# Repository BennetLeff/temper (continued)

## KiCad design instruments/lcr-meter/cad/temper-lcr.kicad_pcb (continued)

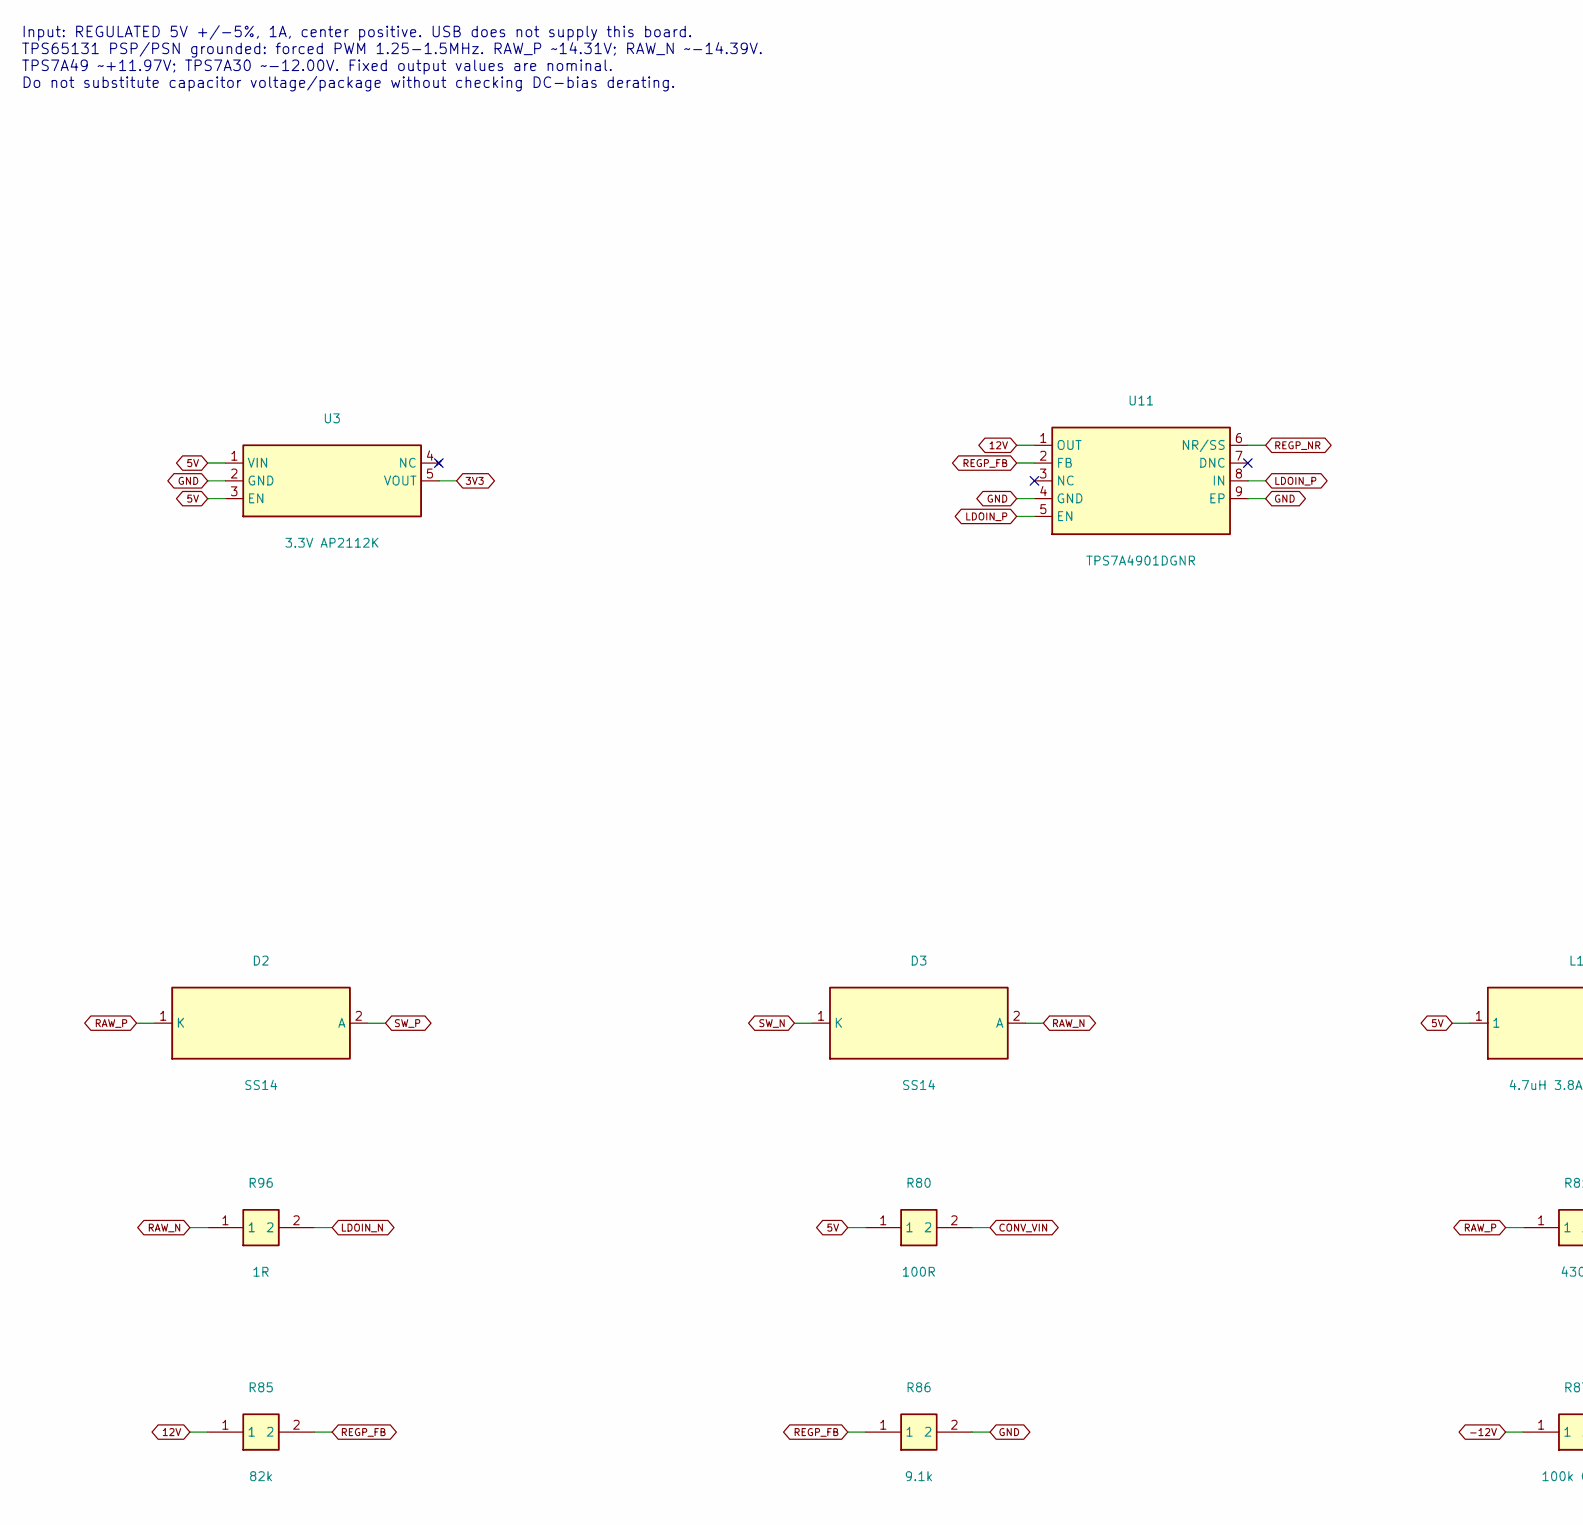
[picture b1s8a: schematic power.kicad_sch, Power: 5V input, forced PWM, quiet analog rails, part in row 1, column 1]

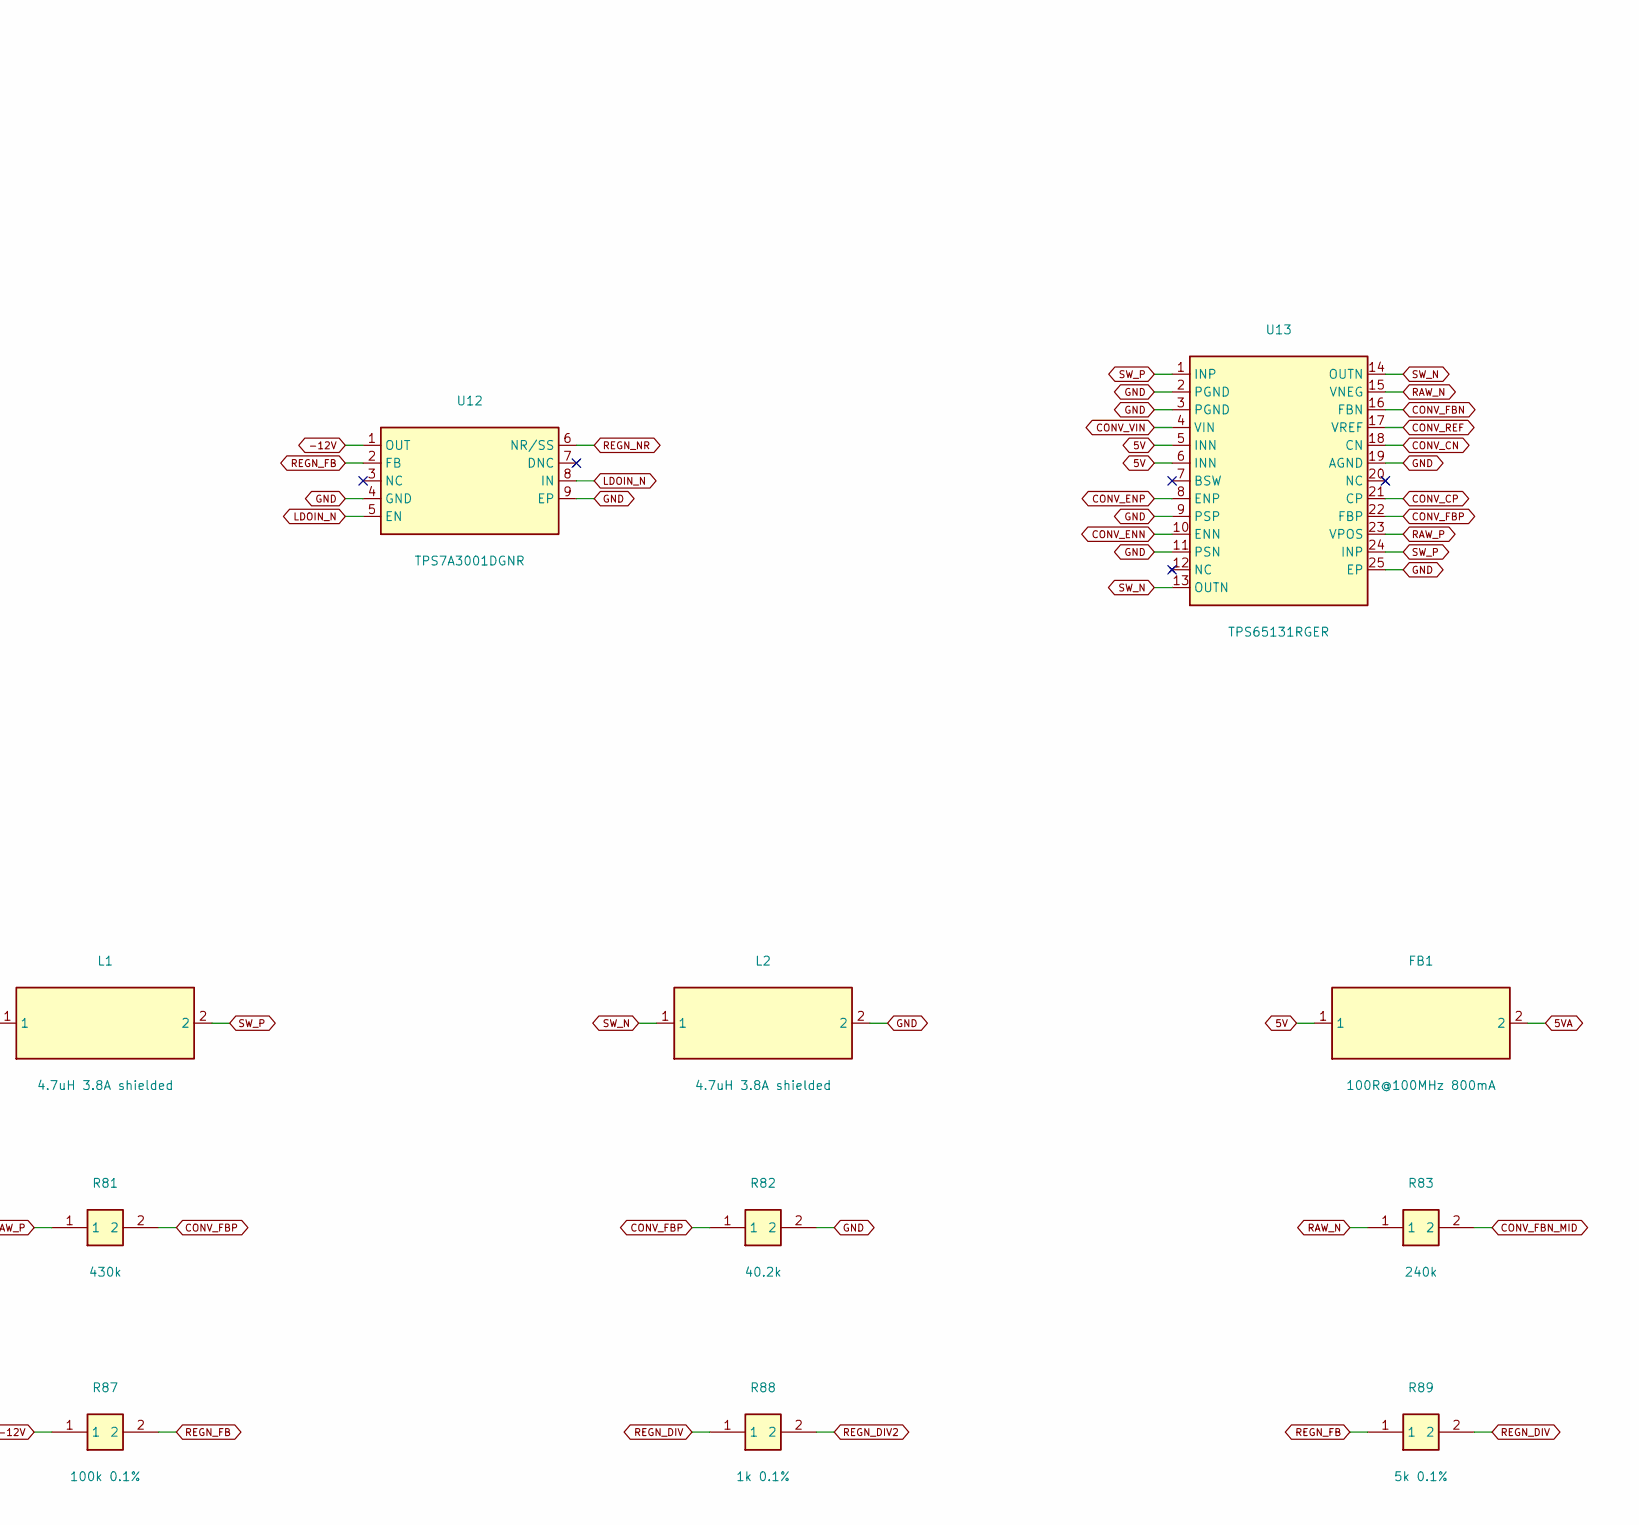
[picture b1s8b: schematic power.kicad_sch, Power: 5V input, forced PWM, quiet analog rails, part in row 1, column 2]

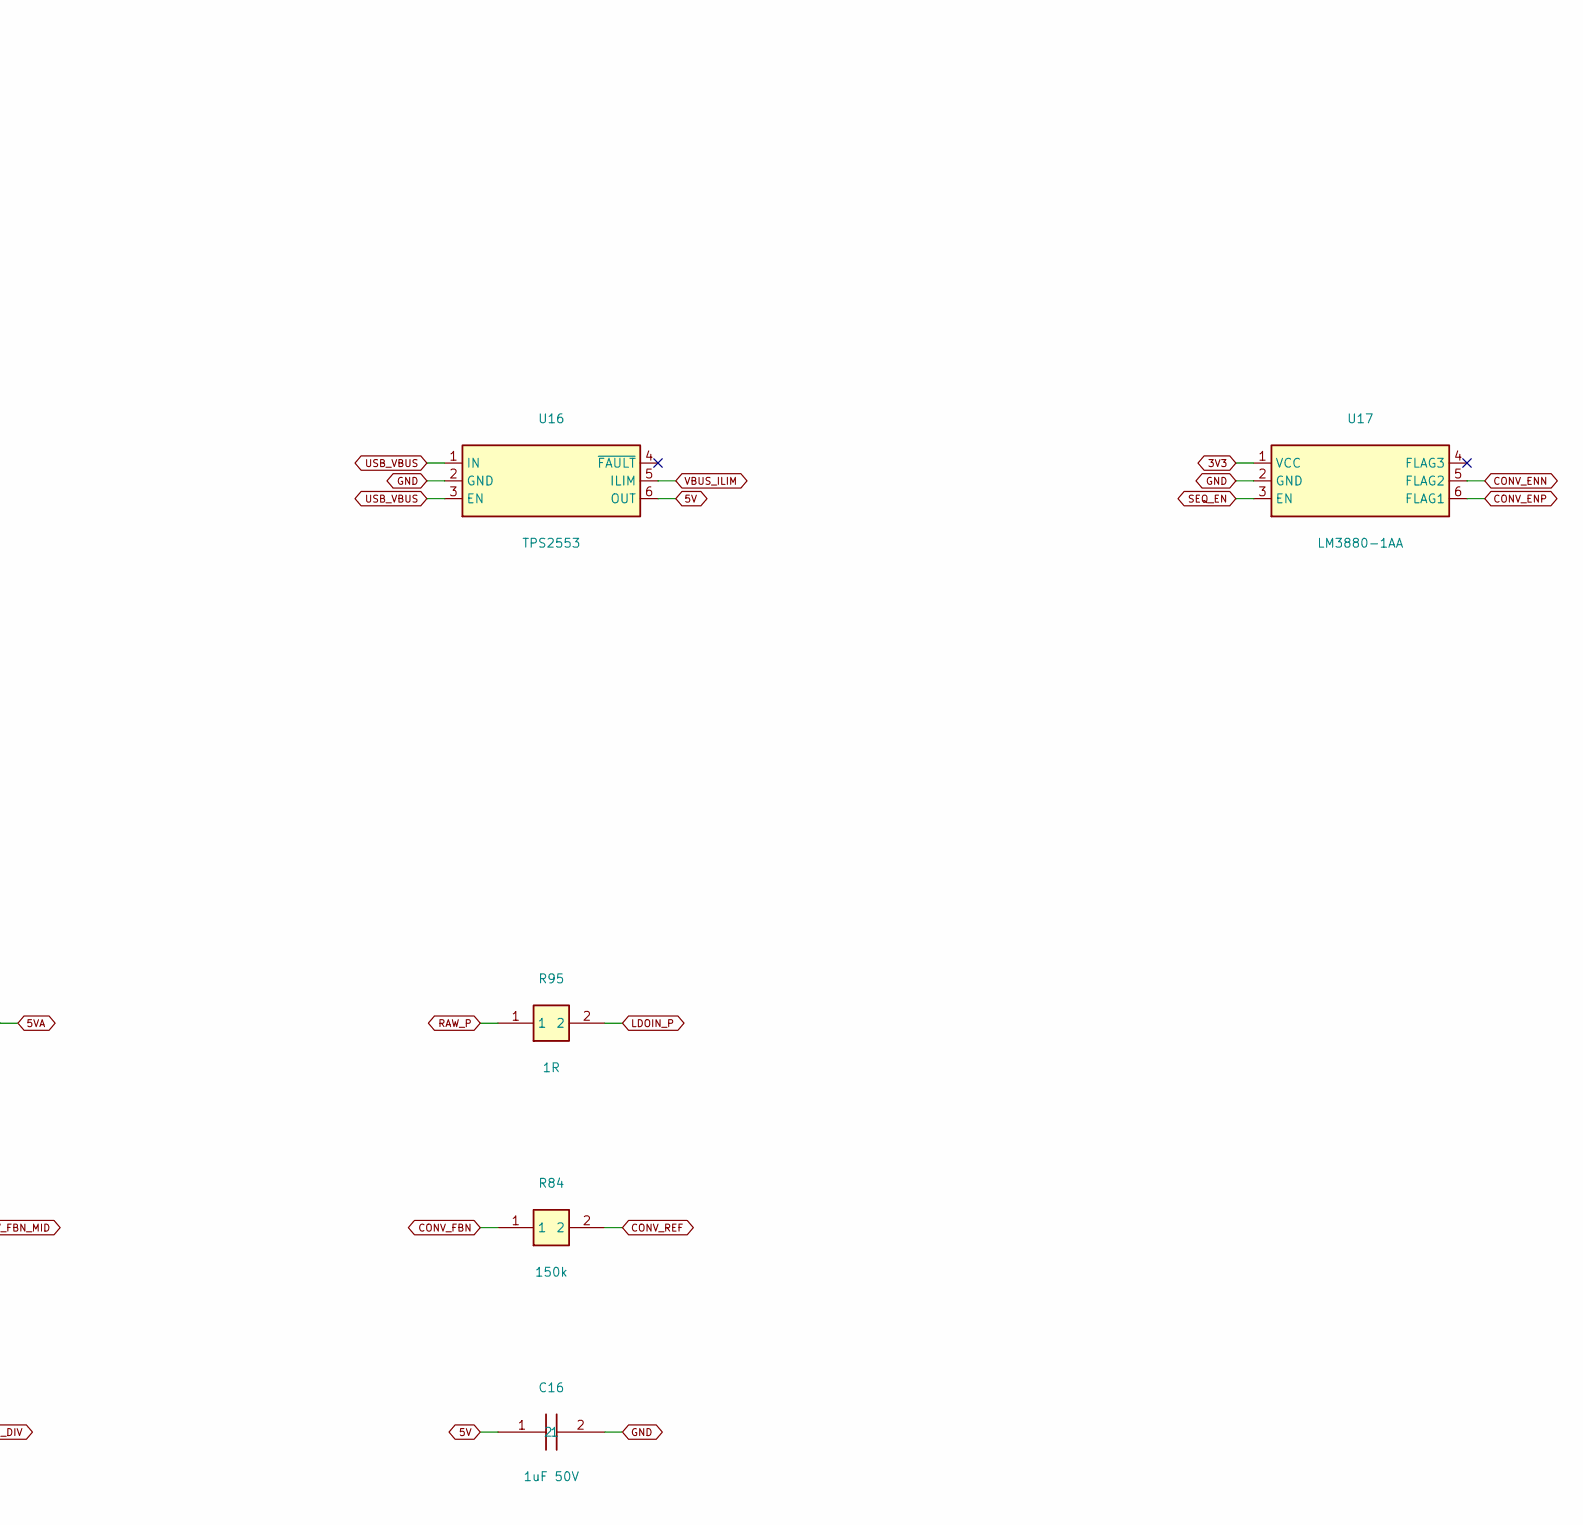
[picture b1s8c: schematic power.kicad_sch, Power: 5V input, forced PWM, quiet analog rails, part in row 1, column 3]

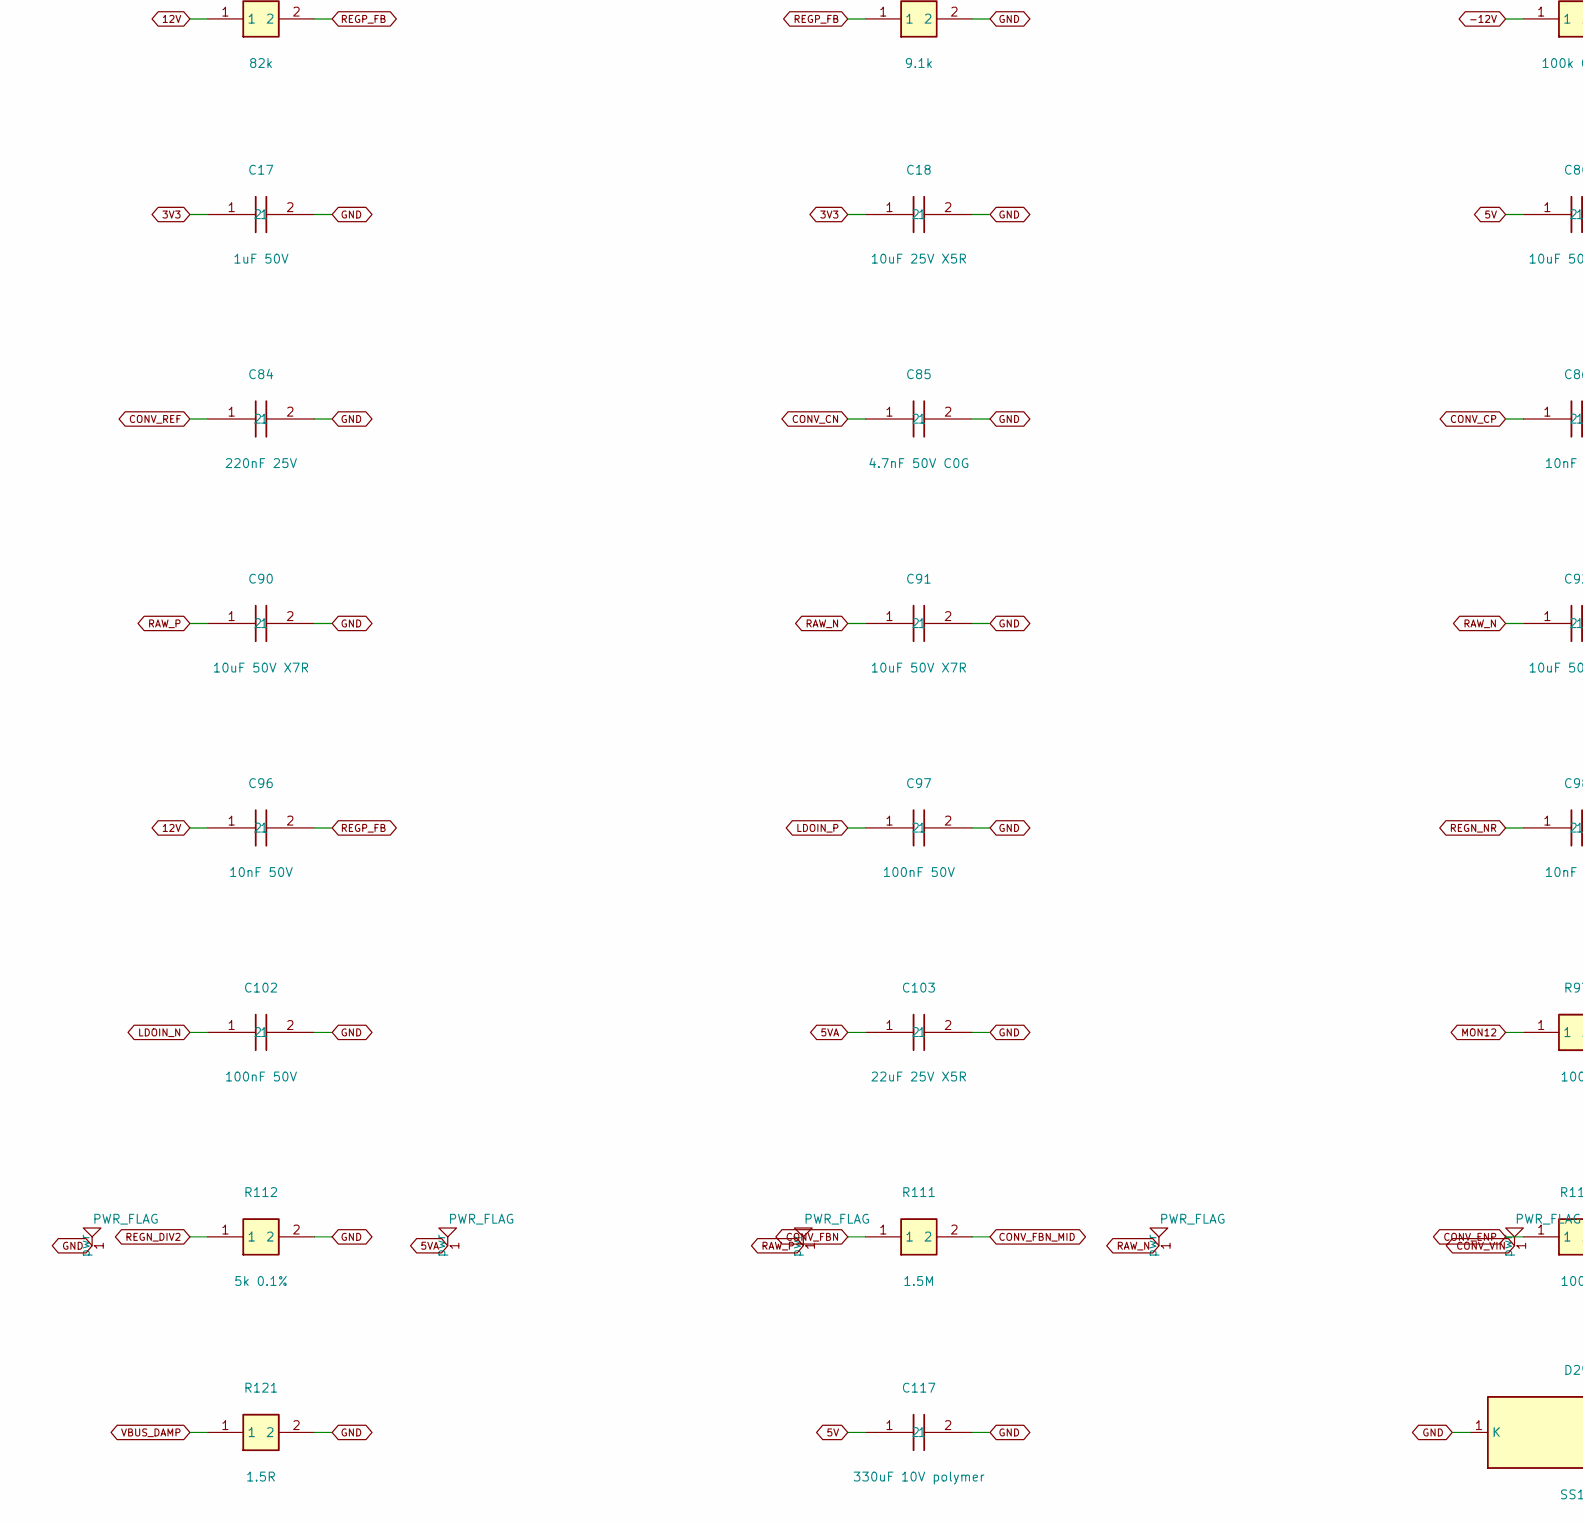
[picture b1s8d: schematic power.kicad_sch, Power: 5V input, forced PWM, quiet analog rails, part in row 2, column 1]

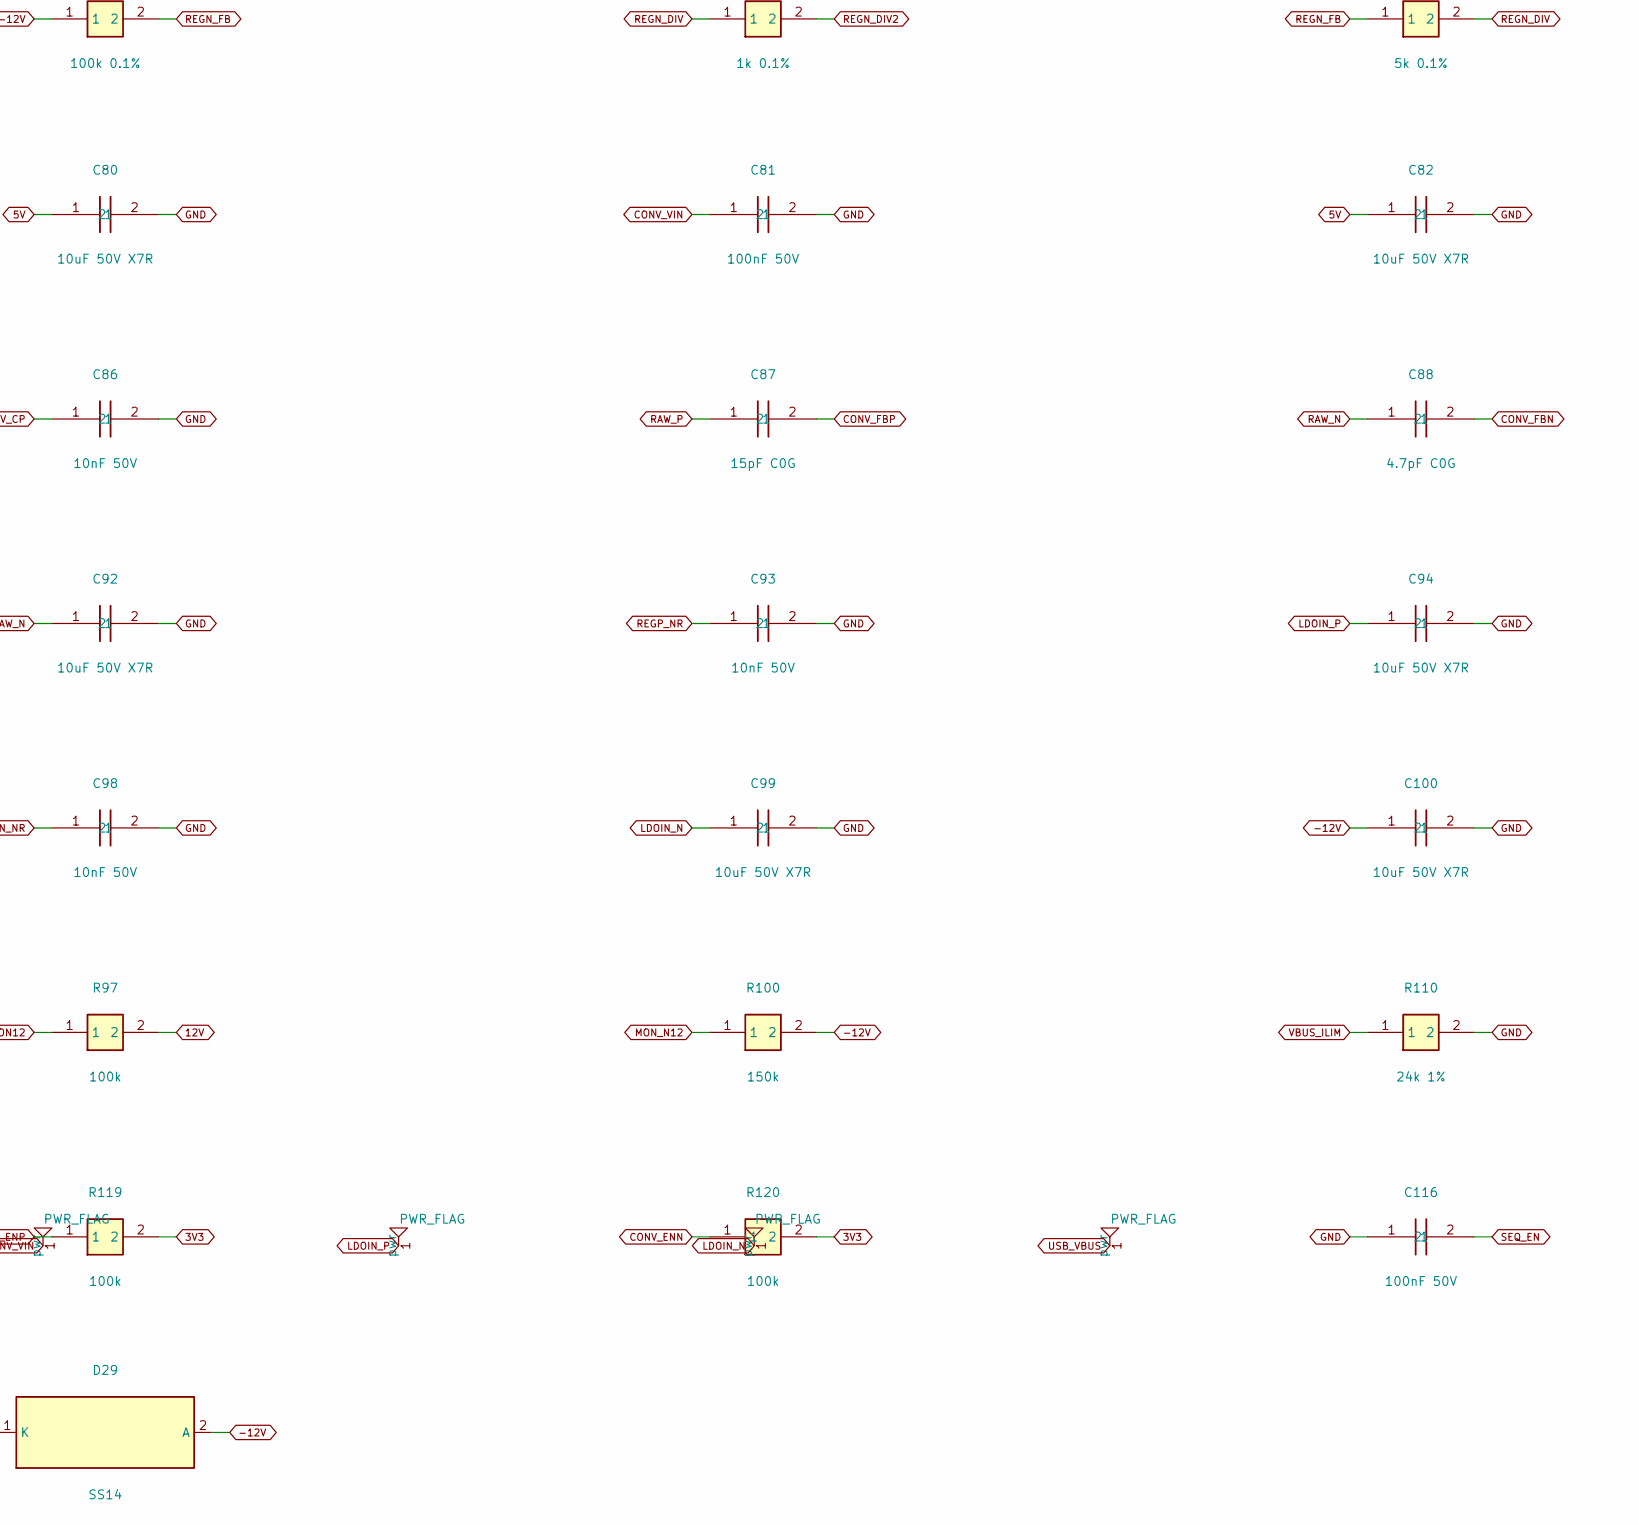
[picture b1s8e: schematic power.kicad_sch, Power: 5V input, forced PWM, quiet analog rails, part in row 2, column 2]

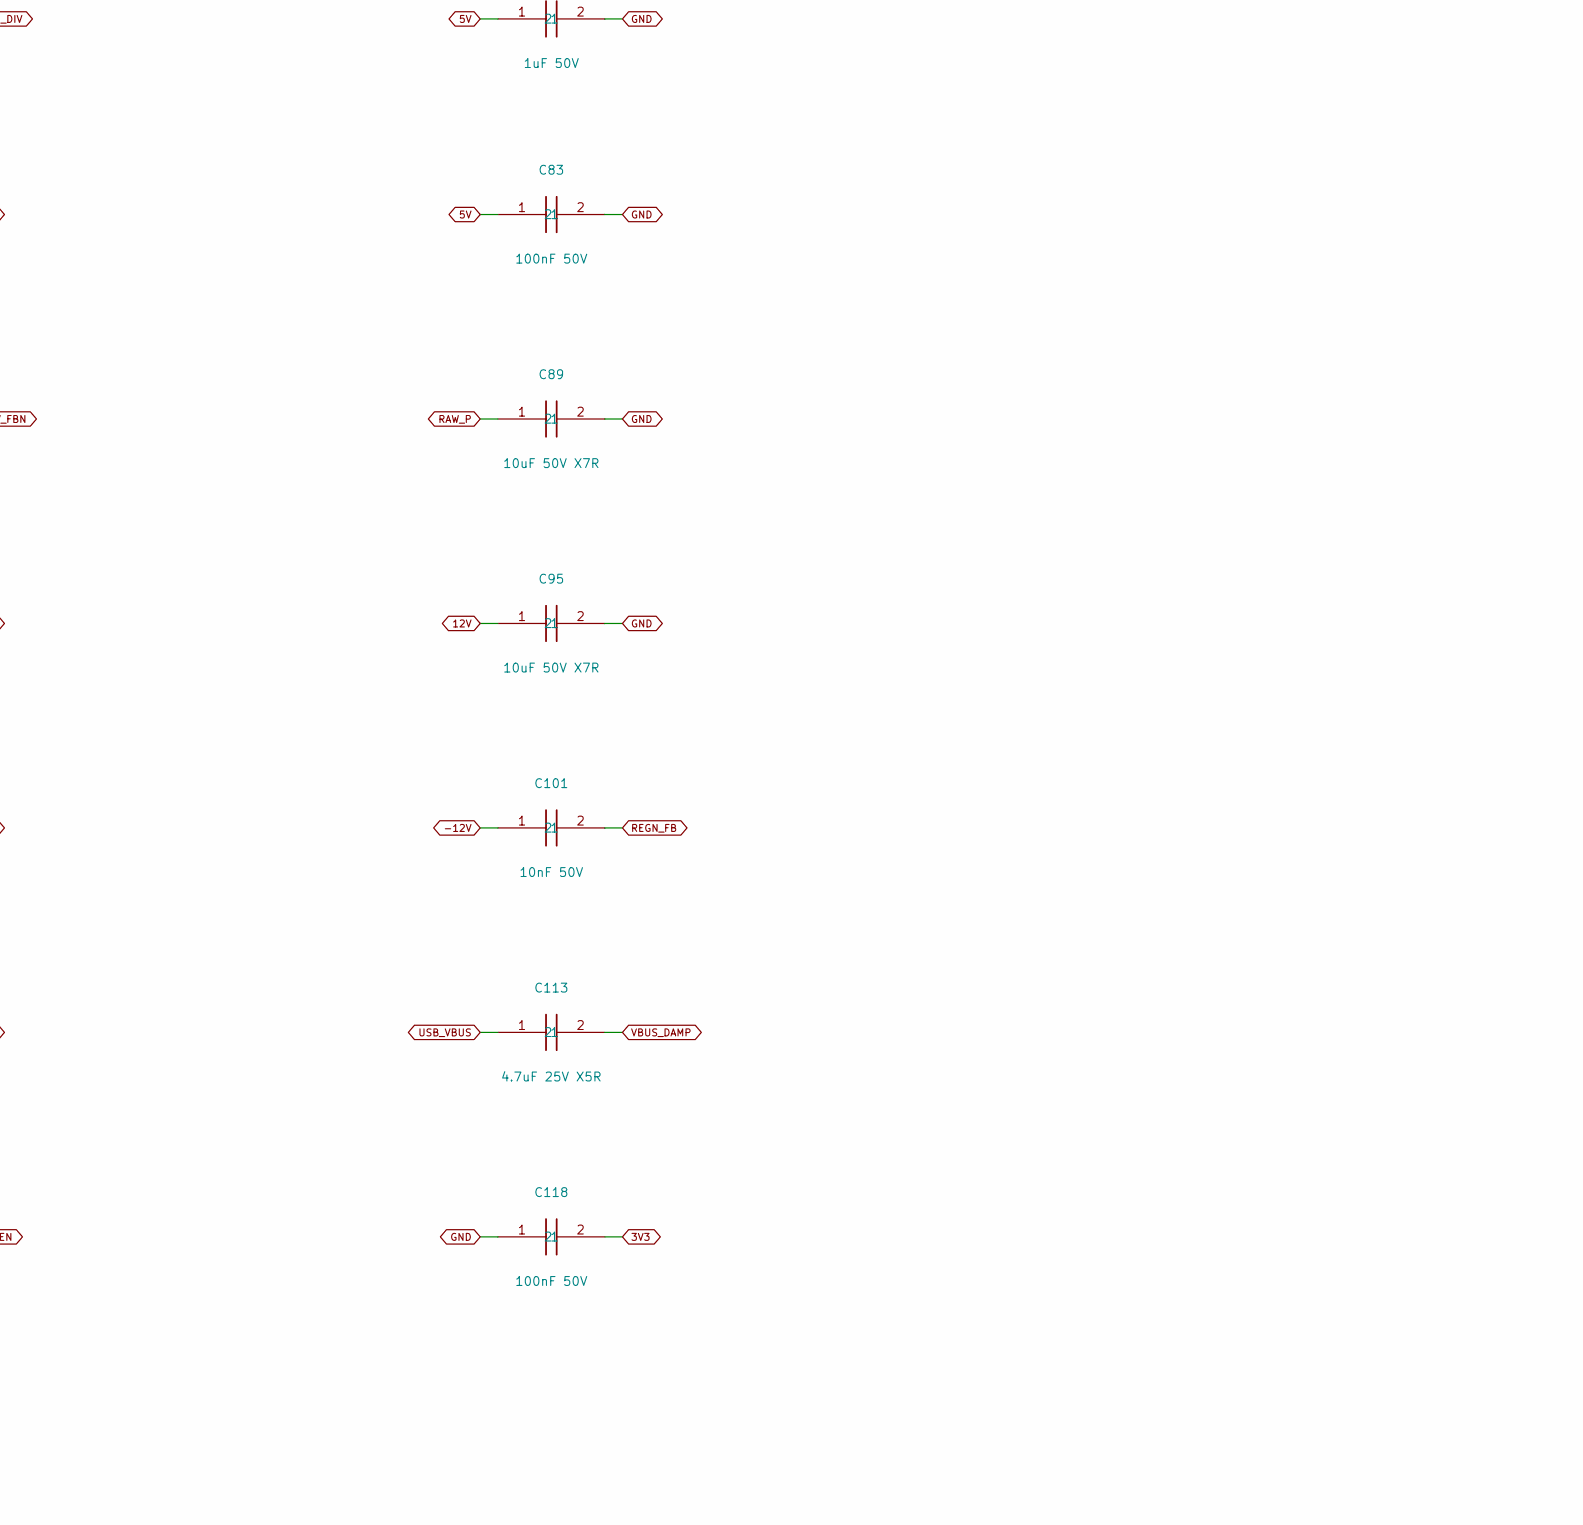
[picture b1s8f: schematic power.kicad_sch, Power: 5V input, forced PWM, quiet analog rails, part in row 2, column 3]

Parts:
C16, C17: 1uF 50V; C_0805_2012Metric; MPN CL21B105KBFNNNE; LCSC C28323
C18: 10uF 25V X5R; C_0805_2012Metric; MPN CL21A106KAYNNNE; LCSC C15850
C80, C82, C89, C90, C91, C92, C94, C95, C99, C100: 10uF 50V X7R; C_1210_3225Metric; MPN CL32B106KBJNNNE; LCSC C138687
C81, C83, C97, C102, C116, C118: 100nF 50V; C_0603_1608Metric; MPN CC0603KRX7R9BB104; LCSC C14663
C84: 220nF 25V; C_0603_1608Metric; MPN CL10B224KA8NNNC; LCSC C21120
C85: 4.7nF 50V C0G; C_0603_1608Metric; MPN CC0603JRNPO9BN472; LCSC C576818
C86, C93, C96, C98, C101: 10nF 50V; C_0603_1608Metric; MPN 0603B103K500NT; LCSC C57112
C87: 15pF C0G; C_0603_1608Metric; MPN CL10C150JB8NNNC; LCSC C1644
C88: 4.7pF C0G; C_0603_1608Metric; MPN 0603CG4R7C500NT; LCSC C1669
C103: 22uF 25V X5R; C_1206_3216Metric; MPN CL31A226KAHNNNE; LCSC C12891
C113: 4.7uF 25V X5R; C_0805_2012Metric; MPN CL21A475KAQNNNE; LCSC C1779
C117: 330uF 10V polymer; CP_Elec_8x6.9; MPN PCG1A331MCL1GS; LCSC C433208
D2, D3, D29: SS14; D_SMA; MPN SS14; LCSC C2480
FB1: 100R@100MHz 800mA; L_0805_2012Metric; MPN GZ2012D101TF; LCSC C1015
L1, L2: 4.7uH 3.8A shielded; L_Changjiang_FNR5040S; MPN FNR5040S4R7MT; LCSC C167963
R80: 100R; R_0603_1608Metric; MPN 0603WAF1000T5E; LCSC C22775
R81: 430k; R_0603_1608Metric; MPN 0603WAF4303T5E; LCSC C25969
R82: 40.2k; R_0603_1608Metric; MPN 0603WAF4022T5E; LCSC C12447
R83: 240k; R_0603_1608Metric; MPN 0603WAF2403T5E; LCSC C4197
R84, R100: 150k; R_0603_1608Metric; MPN 0603WAF1503T5E; LCSC C22807
R85: 82k; R_0603_1608Metric; MPN 0603WAF8202T5E; LCSC C23254
R86: 9.1k; R_0603_1608Metric; MPN 0603WAF9101T5E; LCSC C23260
R87: 100k 0.1%; R_0603_1608Metric; MPN RT0603BRD07100KL; LCSC C122538
R88: 1k 0.1%; R_0603_1608Metric; MPN RT0603BRD071KL; LCSC C110776
R89, R112: 5k 0.1%; R_0603_1608Metric; MPN AR03BTCX5001; LCSC C2828621
R95, R96: 1R; R_0603_1608Metric; MPN 0603WAF100KT5E; LCSC C22936
R97, R119, R120: 100k; R_0603_1608Metric; MPN 0603WAF1003T5E; LCSC C25803
R110: 24k 1%; R_0603_1608Metric; MPN 0603WAF2402T5E; LCSC C23352
R111: 1.5M; R_0603_1608Metric; MPN 0603WAF1504T5E; LCSC C4172
R121: 1.5R; R_0603_1608Metric; MPN 0603WAF150KT5E; LCSC C22769
U3: 3.3V AP2112K; SOT-23-5; MPN AP2112K-3.3TRG1; LCSC C51118
U11: TPS7A4901DGNR; HVSSOP-8-1EP_3x3mm_P0.65mm_EP1.57x1.89mm; MPN TPS7A4901DGNR; LCSC C16430
U12: TPS7A3001DGNR; HVSSOP-8-1EP_3x3mm_P0.65mm_EP1.57x1.89mm; MPN TPS7A3001DGNR; LCSC C33835
U13: TPS65131RGER; VQFN-24-1EP_4x4mm_P0.5mm_EP2.45x2.45mm; MPN TPS65131RGER; LCSC C87663
U16: TPS2553; SOT-23-6; MPN TPS2553DBVR; LCSC C55266
U17: LM3880-1AA; SOT-23-6; MPN LM3880MF-1AA/NOPB; LCSC C486059

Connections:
3V3: C17.1, C18.1, C118.2, R119.2, R120.2, U3.5 (VOUT), U17.1 (VCC); also elsewhere on the board
5V: C16.1, C80.1, C82.1, C83.1, C117.1, FB1.1, L1.1, R80.1, U3.1 (VIN), U3.3 (EN), U13.5 (INN), U13.6 (INN), U16.6 (OUT); also elsewhere on the board
5VA: C103.1, FB1.2; also elsewhere on the board
12V: C95.1, C96.1, R85.1, R97.2, U11.1 (OUT); also elsewhere on the board
-12V: C100.1, C101.1, D29.2 (A), R87.1, R100.2, U12.1 (OUT); also elsewhere on the board
CONV_CN: C85.1, U13.18 (CN)
CONV_CP: C86.1, U13.21 (CP)
CONV_ENN: R120.1, U13.10 (ENN), U17.5 (FLAG2)
CONV_ENP: R119.1, U13.8 (ENP), U17.6 (FLAG1)
CONV_FBN: C88.2, R84.1, R111.1, U13.16 (FBN)
CONV_FBN_MID: R83.2, R111.2
CONV_FBP: C87.2, R81.2, R82.1, U13.22 (FBP)
CONV_REF: C84.1, R84.2, U13.17 (VREF)
CONV_VIN: C81.1, R80.2, U13.4 (VIN)
GND: C16.2, C17.2, C18.2, C80.2, C81.2, C82.2, C83.2, C84.2, C85.2, C86.2, C89.2, C90.2, C91.2, C92.2, C93.2, C94.2, C95.2, C97.2, C98.2, C99.2, C100.2, C102.2, C103.2, C116.1, C117.2, C118.1, D29.1 (K), L2.2, R82.2, R86.2, R110.2, R112.2, R121.2, U3.2 (GND), U11.4 (GND), U11.9 (EP), U12.4 (GND), U12.9 (EP), U13.2 (PGND), U13.3 (PGND), U13.9 (PSP), U13.11 (PSN), U13.19 (AGND), U13.25 (EP), U16.2 (GND), U17.2 (GND); also elsewhere on the board
LDOIN_N: C99.1, C102.1, R96.2, U12.5 (EN), U12.8 (IN)
LDOIN_P: C94.1, C97.1, R95.2, U11.5 (EN), U11.8 (IN)
MON12: R97.1; also elsewhere on the board
MON_N12: R100.1; also elsewhere on the board
RAW_N: C88.1, C91.1, C92.1, D3.2 (A), R83.1, R96.1, U13.15 (VNEG); also elsewhere on the board
RAW_P: C87.1, C89.1, C90.1, D2.1 (K), R81.1, R95.1, U13.23 (VPOS); also elsewhere on the board
REGN_DIV: R88.1, R89.2
REGN_DIV2: R88.2, R112.1
REGN_FB: C101.2, R87.2, R89.1, U12.2 (FB)
REGN_NR: C98.1, U12.6 (NR/SS)
REGP_FB: C96.2, R85.2, R86.1, U11.2 (FB)
REGP_NR: C93.1, U11.6 (NR/SS)
SEQ_EN: C116.2, U17.3 (EN)
SW_N: D3.1 (K), L2.1, U13.13 (OUTN), U13.14 (OUTN)
SW_P: D2.2 (A), L1.2, U13.1 (INP), U13.24 (INP)
USB_VBUS: C113.1, U16.1 (IN), U16.3 (EN); also elsewhere on the board
VBUS_DAMP: C113.2, R121.1
VBUS_ILIM: R110.1, U16.5 (ILIM)

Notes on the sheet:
Input: REGULATED 5V +/-5%, 1A, center positive. USB does not supply this board. TPS65131 PSP/PSN grounded: forced PWM 1.25-1.5MHz. RAW_P ~14.31V; RAW_N ~-14.39V. TPS7A49 ~+11.97V; TPS7A30 ~-12.00V. Fixed output values are nominal. Do not substitute capacitor voltage/package without checking DC-bias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
